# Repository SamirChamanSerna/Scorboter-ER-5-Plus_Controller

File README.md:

# Scorboter-ER-5-Plus_Controller
Scorboter-ER 5 Plus Controller
⚠️Development has been halted⚠️

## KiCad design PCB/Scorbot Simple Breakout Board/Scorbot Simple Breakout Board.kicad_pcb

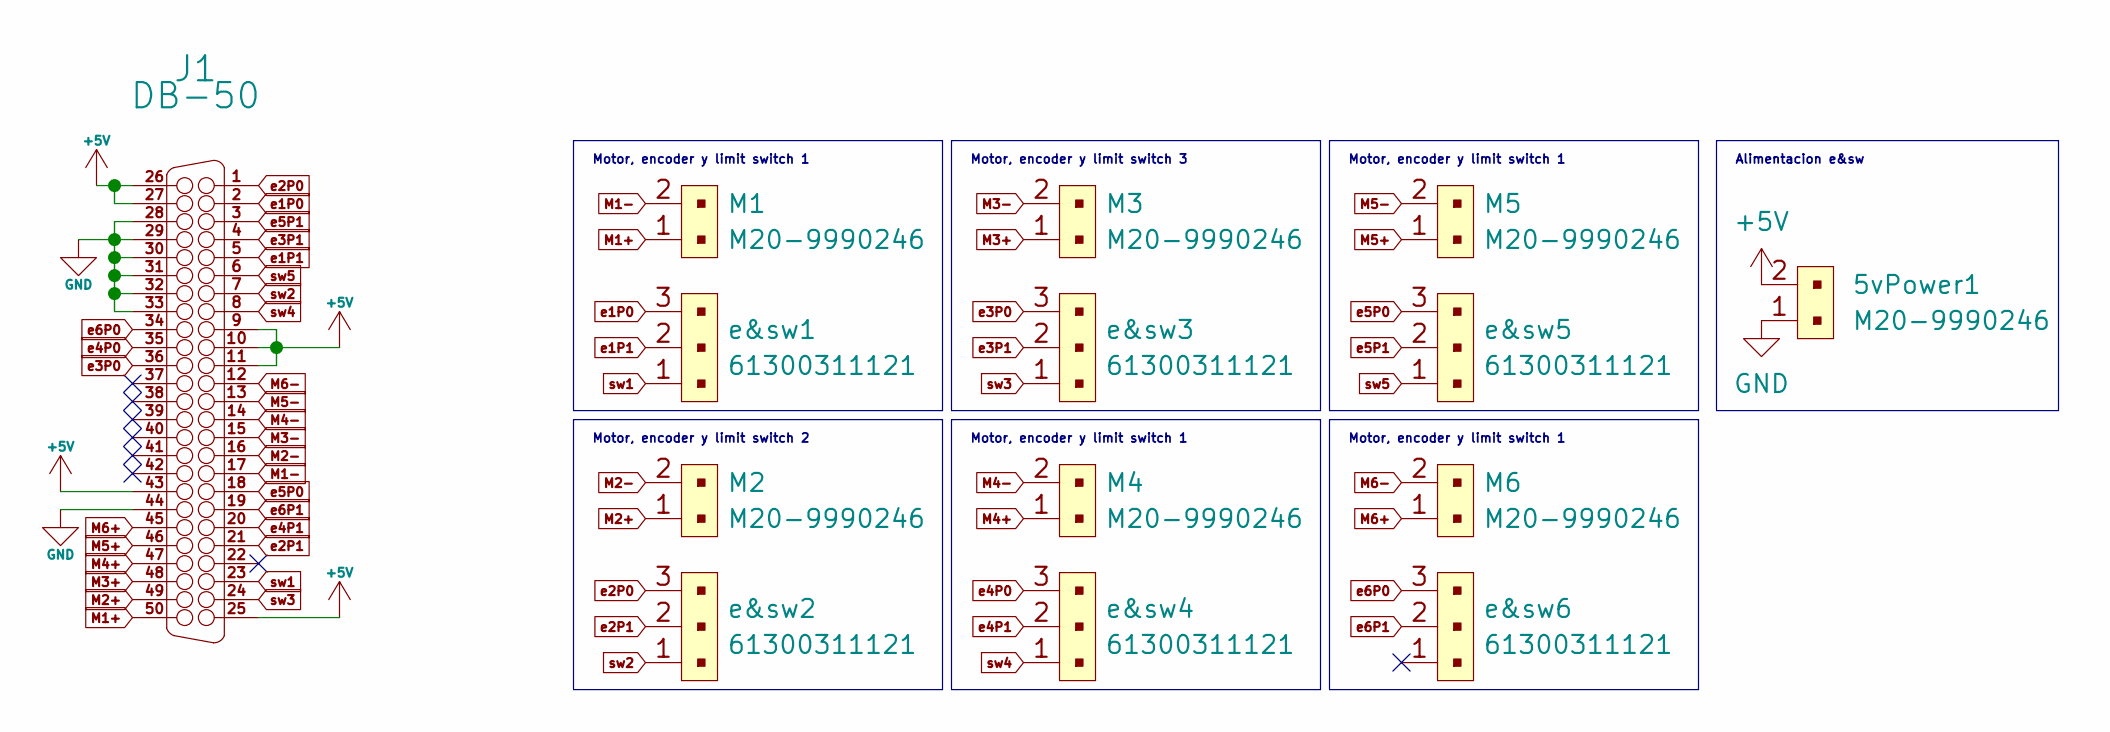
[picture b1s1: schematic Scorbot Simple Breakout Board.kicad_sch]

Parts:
5vPower1: M20-9990246; PinSocket_1x02_P2.54mm_Vertical; MPN M20-9990246; Digi-Key_PN 952-2262-ND
J1: DB-50; AMPHENOL_DD50S564TLF
M1, M2, M3, M4, M5, M6: M20-9990246; PinSocket_1x02_P2.54mm_Vertical; MPN M20-9990246; Digi-Key_PN 952-2262-ND
e&sw1, e&sw2, e&sw3, e&sw4, e&sw5, e&sw6: 61300311121; PinSocket_1x03_P2.54mm_Vertical; MPN 61300311121; Digi-Key_PN 732-5316-ND

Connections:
+5V: 5vPower1.2, J1.9, J1.10, J1.11, J1.25, J1.26, J1.27, J1.43; also elsewhere on the board
GND: 5vPower1.1, J1.28, J1.29, J1.30, J1.31, J1.32, J1.33, J1.44; also elsewhere on the board
M1+: J1.50, M1.1
M1-: J1.17, M1.2
M2+: J1.49, M2.1
M2-: J1.16, M2.2
M3+: J1.48, M3.1
M3-: J1.15, M3.2
M4+: J1.47, M4.1
M4-: J1.14, M4.2
M5+: J1.46, M5.1
M5-: J1.13, M5.2
M6+: J1.45, M6.1
M6-: J1.12, M6.2
e1P0: J1.2, e&sw1.3
e1P1: J1.5, e&sw1.2
e2P0: J1.1, e&sw2.3
e2P1: J1.21, e&sw2.2
e3P0: J1.36, e&sw3.3
e3P1: J1.4, e&sw3.2
e4P0: J1.35, e&sw4.3
e4P1: J1.20, e&sw4.2
e5P0: J1.18, e&sw5.3
e5P1: J1.3, e&sw5.2
e6P0: J1.34, e&sw6.3
e6P1: J1.19, e&sw6.2
sw1: J1.23, e&sw1.1
sw2: J1.7, e&sw2.1
sw3: J1.24, e&sw3.1
sw4: J1.8, e&sw4.1
sw5: J1.6, e&sw5.1

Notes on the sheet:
Alimentacion e&sw
Motor, encoder y limit switch 1
Motor, encoder y limit switch 3
Motor, encoder y limit switch 2

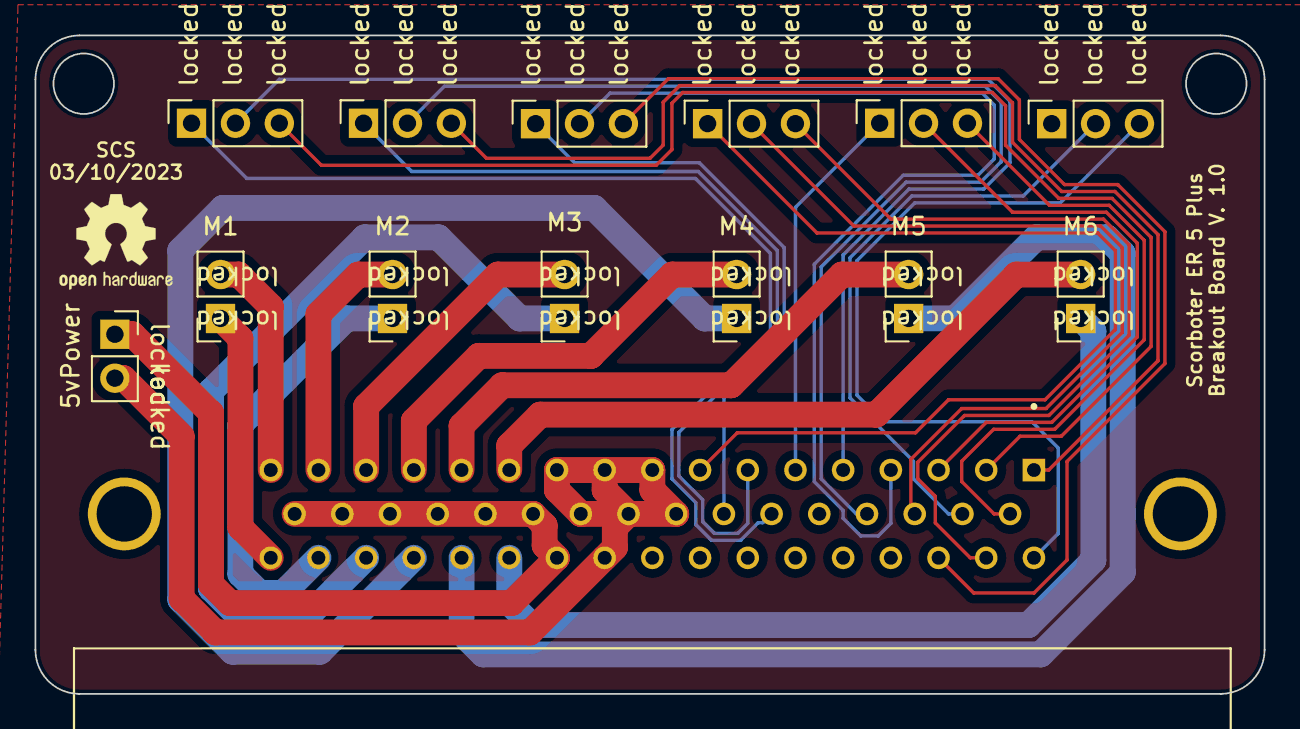
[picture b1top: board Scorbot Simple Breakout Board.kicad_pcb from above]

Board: 2 copper layers, 71.1 x 38.1 mm, 14 parts (0 on the bottom side), 31 nets.

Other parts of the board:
5vPower: M20-9990246; PinSocket_1x02_P2.54mm_Vertical

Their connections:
+5V: 5vPower.2; also elsewhere on the board
GND: 5vPower.1; also elsewhere on the board

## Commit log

2023-10-03 Simple Breakout Board v1
2023-10-30 Test Code
